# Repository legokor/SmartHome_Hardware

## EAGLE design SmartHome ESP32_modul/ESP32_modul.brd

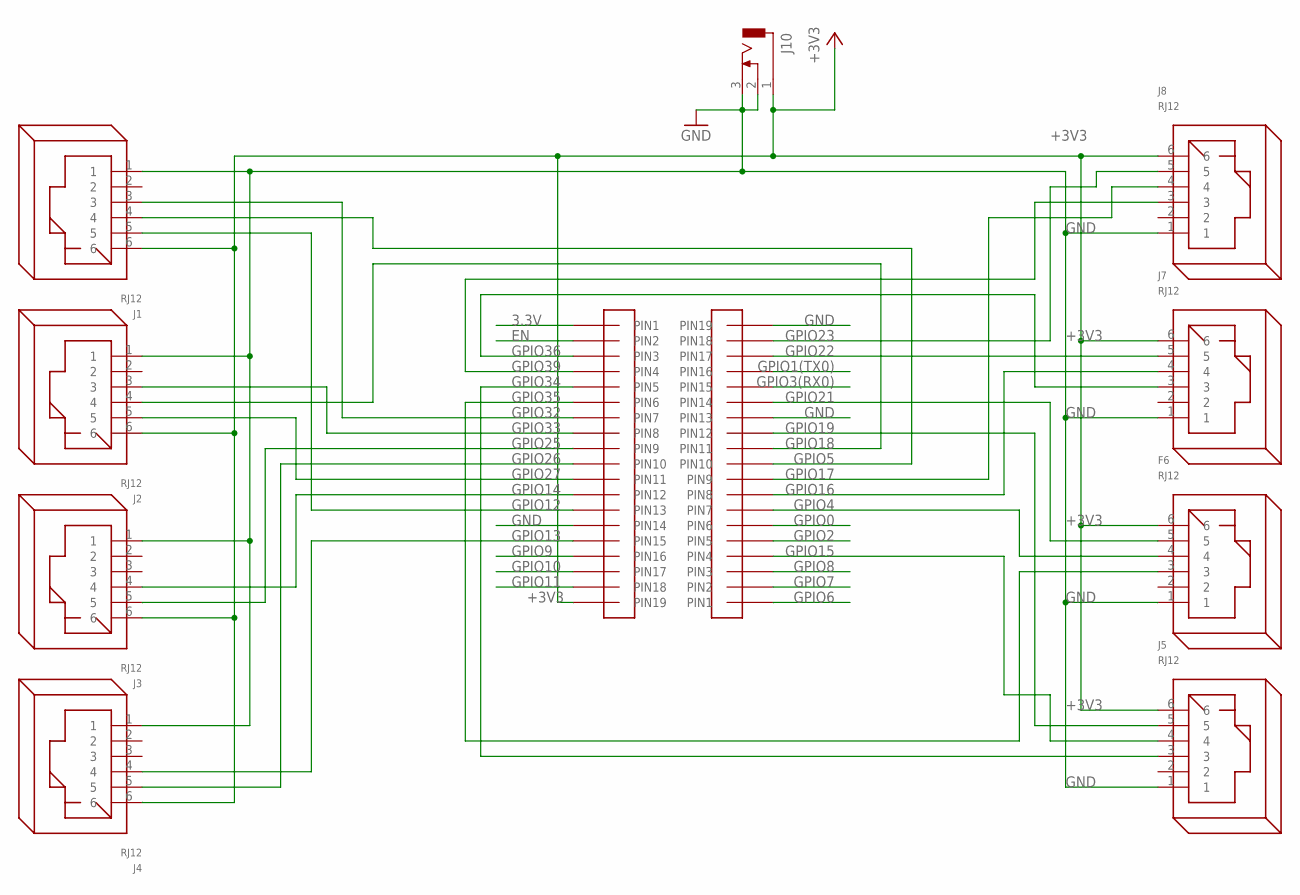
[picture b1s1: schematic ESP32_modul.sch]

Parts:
F6: RJ12
J1, J2, J3, J4, J5, J7, J8: RJ12
J10: DCJ0303
U$1, U$2: F-1X19

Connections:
3.3V: U$1.P$1 (PIN1)
+3V3: F6.6, J1.6, J2.6, J3.6, J4.6, J5.6, J7.6, J8.6, J10.1, U$1.P$19 (PIN19)
EN: U$1.P$2 (PIN2)
GND: F6.1, J1.1, J2.1, J3.1, J4.1, J5.1, J7.1, J8.1, J10.2, J10.3, U$1.P$14 (PIN14), U$2.P$13 (PIN13), U$2.P$19 (PIN19)
GPIO0: U$2.P$6 (PIN6)
GPIO1(TX0): U$2.P$16 (PIN16)
GPIO2: U$2.P$5 (PIN5)
GPIO3(RX0): U$2.P$15 (PIN15)
GPIO4: F6.4, U$2.P$7 (PIN7)
GPIO5: J1.4, U$2.P$10 (PIN10)
GPIO6: U$2.P$1 (PIN1)
GPIO7: U$2.P$2 (PIN2)
GPIO8: U$2.P$3 (PIN3)
GPIO9: U$1.P$16 (PIN16)
GPIO10: U$1.P$17 (PIN17)
GPIO11: U$1.P$18 (PIN18)
GPIO12: J1.5, U$1.P$13 (PIN13)
GPIO13: J4.4, U$1.P$15 (PIN15)
GPIO14: J3.4, U$1.P$12 (PIN12)
GPIO15: J5.4, U$2.P$4 (PIN4)
GPIO16: J7.4, U$2.P$8 (PIN8)
GPIO17: J8.4, U$2.P$9 (PIN9)
GPIO18: J2.4, U$2.P$11 (PIN11)
GPIO19: J5.5, U$2.P$12 (PIN12)
GPIO21: F6.5, U$2.P$14 (PIN14)
GPIO22: J7.5, U$2.P$17 (PIN17)
GPIO23: J8.5, U$2.P$18 (PIN18)
GPIO25: J3.5, U$1.P$9 (PIN9)
GPIO26: J4.5, U$1.P$10 (PIN10)
GPIO27: J2.5, U$1.P$11 (PIN11)
GPIO32: J1.3, U$1.P$7 (PIN7)
GPIO33: J2.3, U$1.P$8 (PIN8)
GPIO34: J5.3, U$1.P$5 (PIN5)
GPIO35: F6.3, U$1.P$6 (PIN6)
GPIO36: J7.3, U$1.P$3 (PIN3)
GPIO39: J8.3, U$1.P$4 (PIN4)

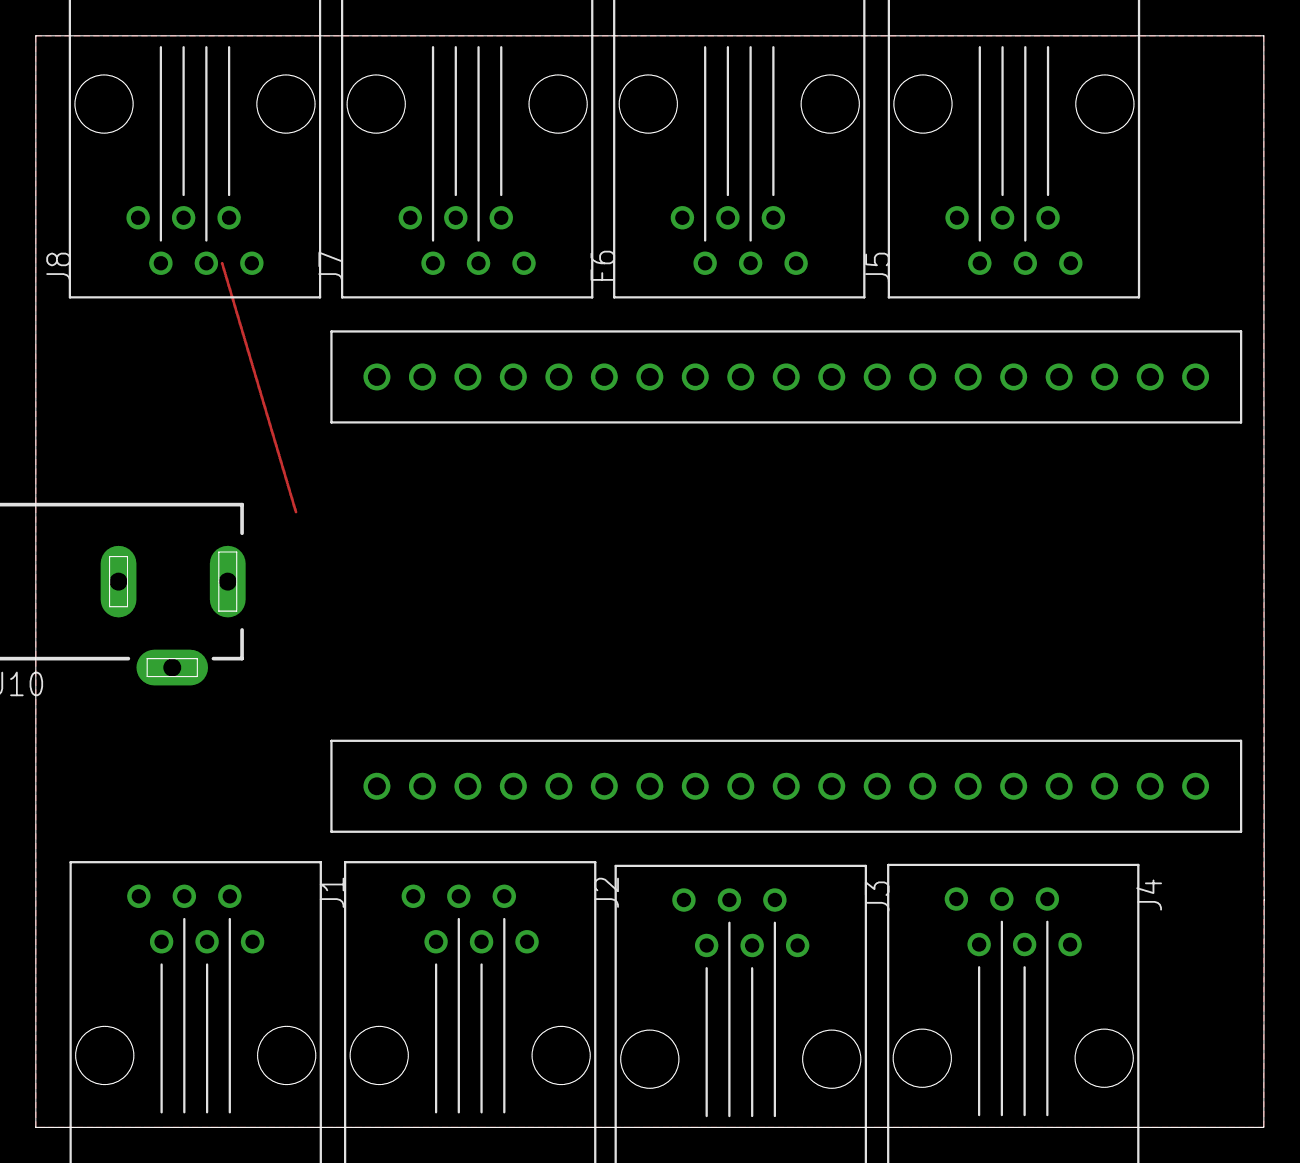
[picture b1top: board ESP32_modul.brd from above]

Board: 2 copper layers, 68.6 x 61.0 mm, 11 parts (0 on the bottom side), 24 nets.

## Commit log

2019-04-02 Add files via upload
    Ez tartalmazza az RJ12 csatlakozót.
